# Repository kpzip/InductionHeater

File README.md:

# InductionHeater
Induction Heater

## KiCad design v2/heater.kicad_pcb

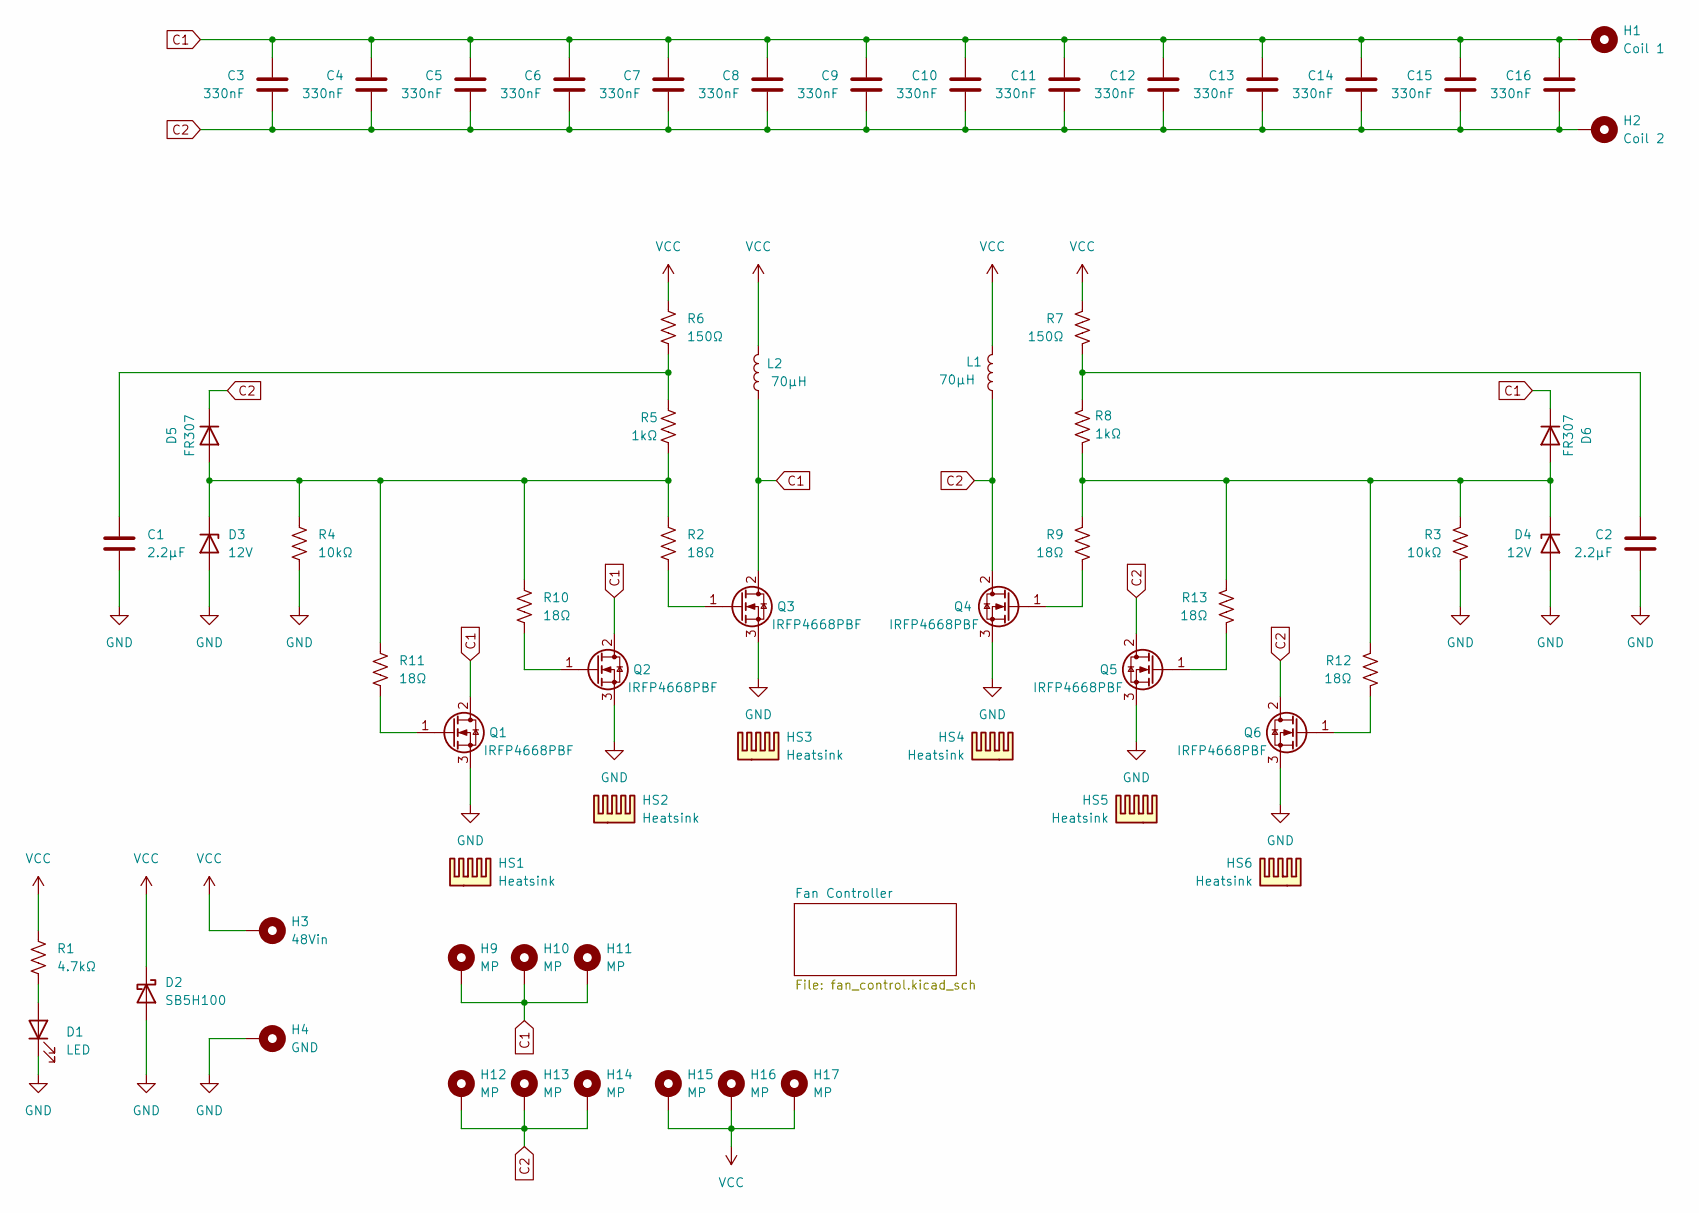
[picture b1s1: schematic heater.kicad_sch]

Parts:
C1, C2: 2.2μF; C_Disc_D4.3mm_W1.9mm_P5.00mm; Manufacturer Part Number FG26X7S2A225KRT06
C3, C4, C5, C6, C7, C8, C9, C10, C11, C12, C13, C14, C15, C16: 330nF; C_Rect_L31.5mm_W15.0mm_P27.50mm_MKS4; Manufacturer Part Number MKP1O133306F00KSSD
D1: LED; LED_D5.0mm; Manufacturer Part Number WP7113ID
D2: SB5H100; D_DO-201AD_P15.24mm_Horizontal; Manufacturer Part Number SB5H100-E3/54
D3, D4: 12V; D_DO-15_P15.24mm_Horizontal; Manufacturer Part Number 1N5349BRLG
D5, D6: FR307; D_DO-201AD_P15.24mm_Horizontal; Manufacturer Part Number FR307G
H1: Coil 1; MountingHole_8.4mm_M8_Pad
H2: Coil 2; MountingHole_8.4mm_M8_Pad
H3: 48Vin; MountingHole_8.4mm_M8_Pad
H4: GND; MountingHole_8.4mm_M8_Pad
H9, H10, H11, H12, H13, H14, H15, H16, H17: MP; MountingHole_3.2mm_M3_DIN965_Pad
HS1, HS2, HS3, HS4, HS5, HS6: Heatsink; 694-50; Manufacturer Part Number 694-50
L1, L2: 70μH; L_Toroid_Vertical_L39.9mm_W32.4mm_P30.0mm
Q1, Q2, Q3, Q4, Q5, Q6: IRFP4668PBF; TO-247-3_Vertical; Manufacturer Part Number IRFP4668PBFXKMA1
R1: 4.7kΩ; R_Axial_DIN0207_L6.3mm_D2.5mm_P10.16mm_Horizontal; Manufacturer Part Number CF12JT4K70
R2, R9, R10, R11, R12, R13: 18Ω; R_Axial_DIN0207_L6.3mm_D2.5mm_P10.16mm_Horizontal; Manufacturer Part Number CFR-50JB-52-18R
R3, R4: 10kΩ; R_Axial_DIN0207_L6.3mm_D2.5mm_P10.16mm_Horizontal; Manufacturer Part Number CF12JT10K0
R5, R8: 1kΩ; R_Axial_DIN0918_L18.0mm_D9.0mm_P30.48mm_Horizontal
R6, R7: 150Ω; R_Axial_DIN0918_L18.0mm_D9.0mm_P30.48mm_Horizontal

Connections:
C1: C3.1, C4.1, C5.1, C6.1, C7.1, C8.1, C9.1, C10.1, C11.1, C12.1, C13.1, C14.1, C15.1, C16.1, D6.1 (K), H1.1 (1_1), H9.1 (1_1), H10.1 (1_1), H11.1 (1_1), L2.1, Q1.2 (D), Q2.2 (D), Q3.2 (D)
C2: C3.2, C4.2, C5.2, C6.2, C7.2, C8.2, C9.2, C10.2, C11.2, C12.2, C13.2, C14.2, C15.2, C16.2, D5.1 (K), H2.1 (1_1), H12.1 (1_1), H13.1 (1_1), H14.1 (1_1), L1.1, Q4.2 (D), Q5.2 (D), Q6.2 (D)
GND: C1.2, C2.2, D1.1 (K), D2.2 (A), D3.2 (A), D4.2 (A), H4.1 (1_1), Q1.3 (S), Q2.3 (S), Q3.3 (S), Q4.3 (S), Q5.3 (S), Q6.3 (S), R3.2, R4.2; also elsewhere on the board
unnamed: C1.1, R5.1, R6.2
unnamed: C2.1, R7.2, R8.1
unnamed: D1.2 (A), R1.2
unnamed: D3.1 (K), D5.2 (A), R2.1, R4.1, R5.2, R10.1, R11.1
unnamed: D4.1 (K), D6.2 (A), R3.1, R8.2, R9.1, R12.1, R13.1
unnamed: Q1.1 (G), R11.2
unnamed: Q2.1 (G), R10.2
unnamed: Q3.1 (G), R2.2
unnamed: Q4.1 (G), R9.2
unnamed: Q5.1 (G), R13.2
unnamed: Q6.1 (G), R12.2
VCC: D2.1 (K), H3.1 (1_1), H15.1 (1_1), H16.1 (1_1), H17.1 (1_1), L1.2, L2.2, R1.1, R6.1, R7.1; also elsewhere on the board

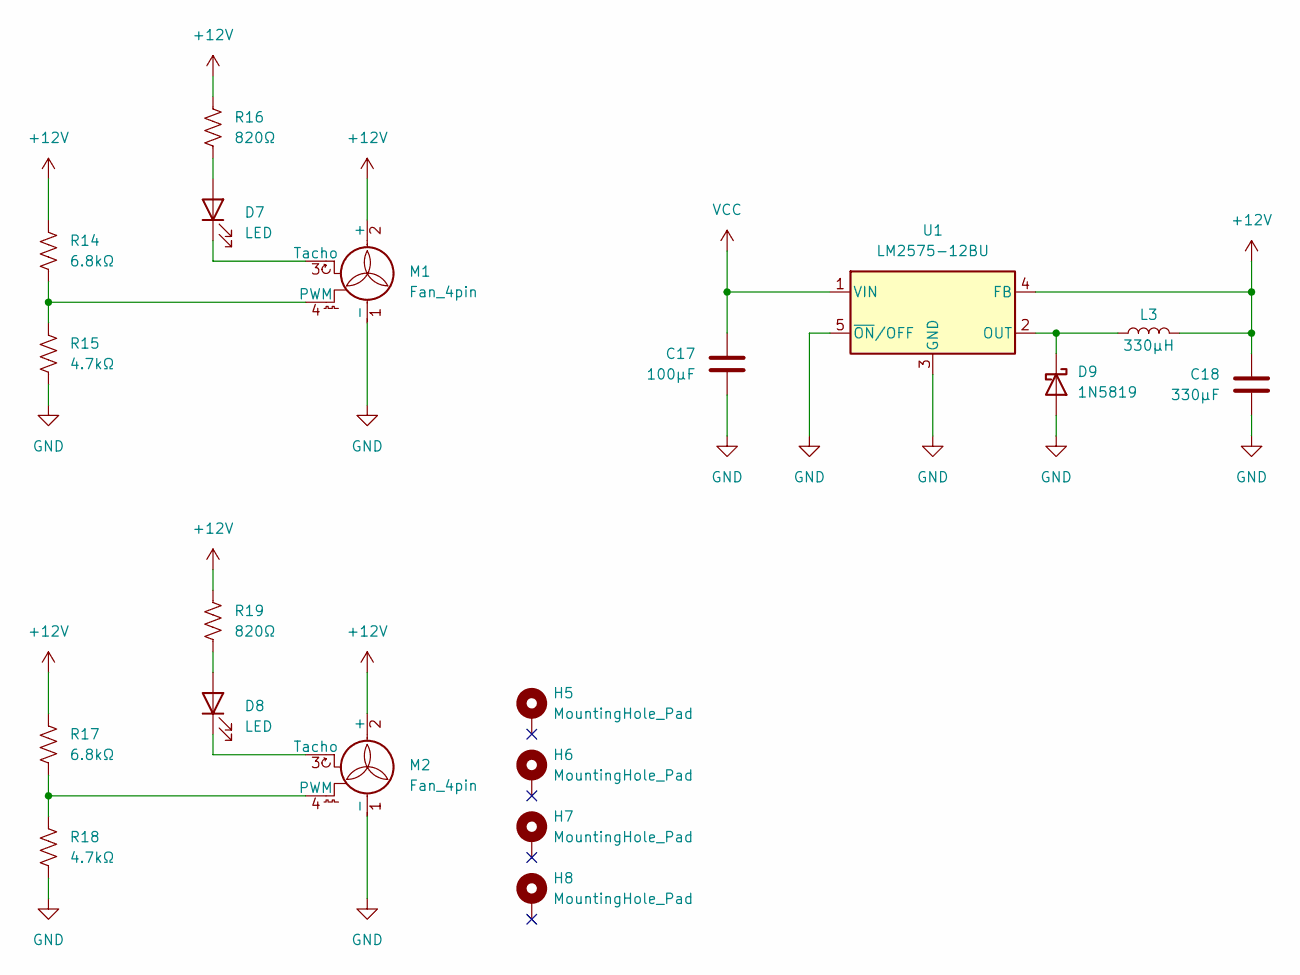
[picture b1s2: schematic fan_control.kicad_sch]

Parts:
C17: 100μF; C_Radial_D10.0mm_H20.0mm_P5.00mm; Manufacturer Part Number 100ZLH100MEFC10X20
C18: 330μF; C_Radial_D12.5mm_H25.0mm_P5.00mm; Manufacturer Part Number UVZ2A331MHD1TO
D7, D8: LED; LED_D5.0mm; Manufacturer Part Number WP7113ID
D9: 1N5819; D_DO-41_SOD81_P10.16mm_Horizontal; Manufacturer Part Number 1N5819
H5, H6, H7, H8: MountingHole_Pad; MountingHole_5.3mm_M5_DIN965_Pad
L3: 330μH; WE-PD_1210; Manufacturer Part Number 7447709331
M1, M2: Fan_4pin; Molex_KK-254_AE-6410-04A_1x04_P2.54mm_Vertical; Manufacturer Part Number 0022292041
R14, R17: 6.8kΩ; R_1206_3216Metric_Pad1.30x1.75mm_HandSolder; Manufacturer Part Number RC1206FR-076K8L
R15, R18: 4.7kΩ; R_1206_3216Metric_Pad1.30x1.75mm_HandSolder; Manufacturer Part Number RC1206FR-074K7L
R16, R19: 820Ω; R_1206_3216Metric_Pad1.30x1.75mm_HandSolder; Manufacturer Part Number CRGCQ1206F820R
U1: LM2575-12BU; TO-263-5_TabPin3; Manufacturer Part Number LM2575HVS-12/NOPB

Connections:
+12V: C18.1, L3.2, M1.2 (+), M2.2 (+), R14.1, R16.1, R17.1, R19.1, U1.4 (FB)
GND: C17.2, C18.2, D9.2 (A), M1.1 (-), M2.1 (-), R15.2, R18.2, U1.3 (GND), U1.5 (~ON/OFF); also elsewhere on the board
unnamed: D7.2 (A), R16.2
unnamed: D7.1 (K), M1.3 (Tacho)
unnamed: D8.2 (A), R19.2
unnamed: D8.1 (K), M2.3 (Tacho)
unnamed: D9.1 (K), L3.1, U1.2 (OUT)
unnamed: M1.4 (PWM), R14.2, R15.1
unnamed: M2.4 (PWM), R17.2, R18.1
VCC: C17.1, U1.1 (VIN); also elsewhere on the board

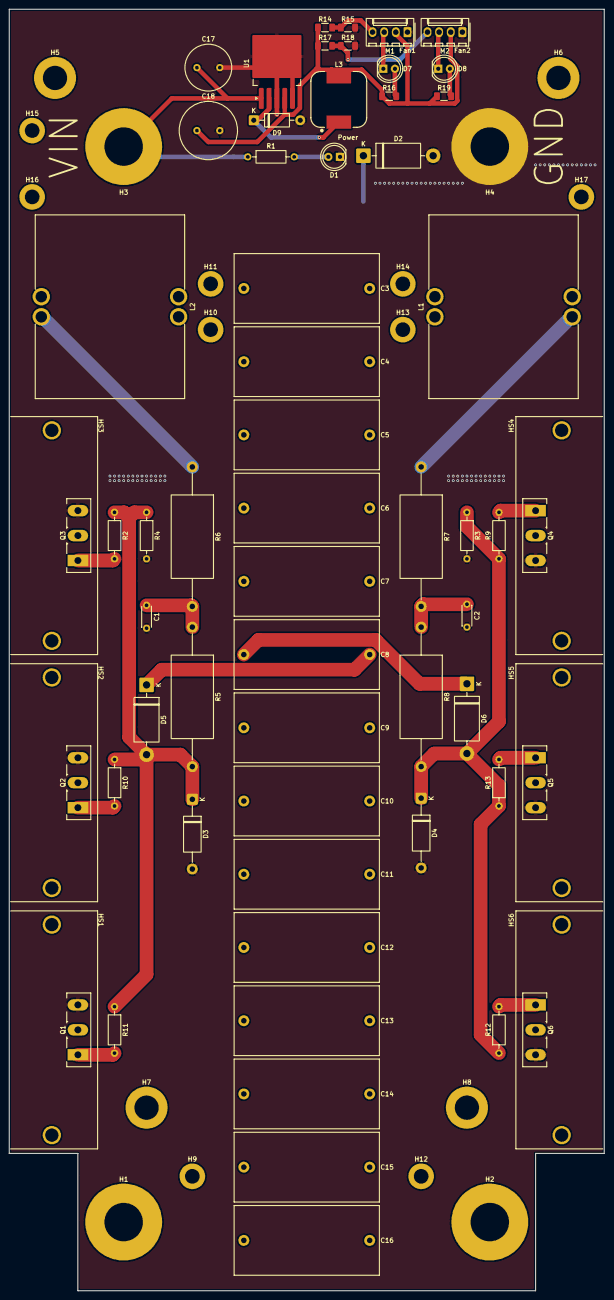
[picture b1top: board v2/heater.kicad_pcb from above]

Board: 2 copper layers, 130.0 x 280.0 mm, 81 parts (0 on the bottom side), 23 nets.

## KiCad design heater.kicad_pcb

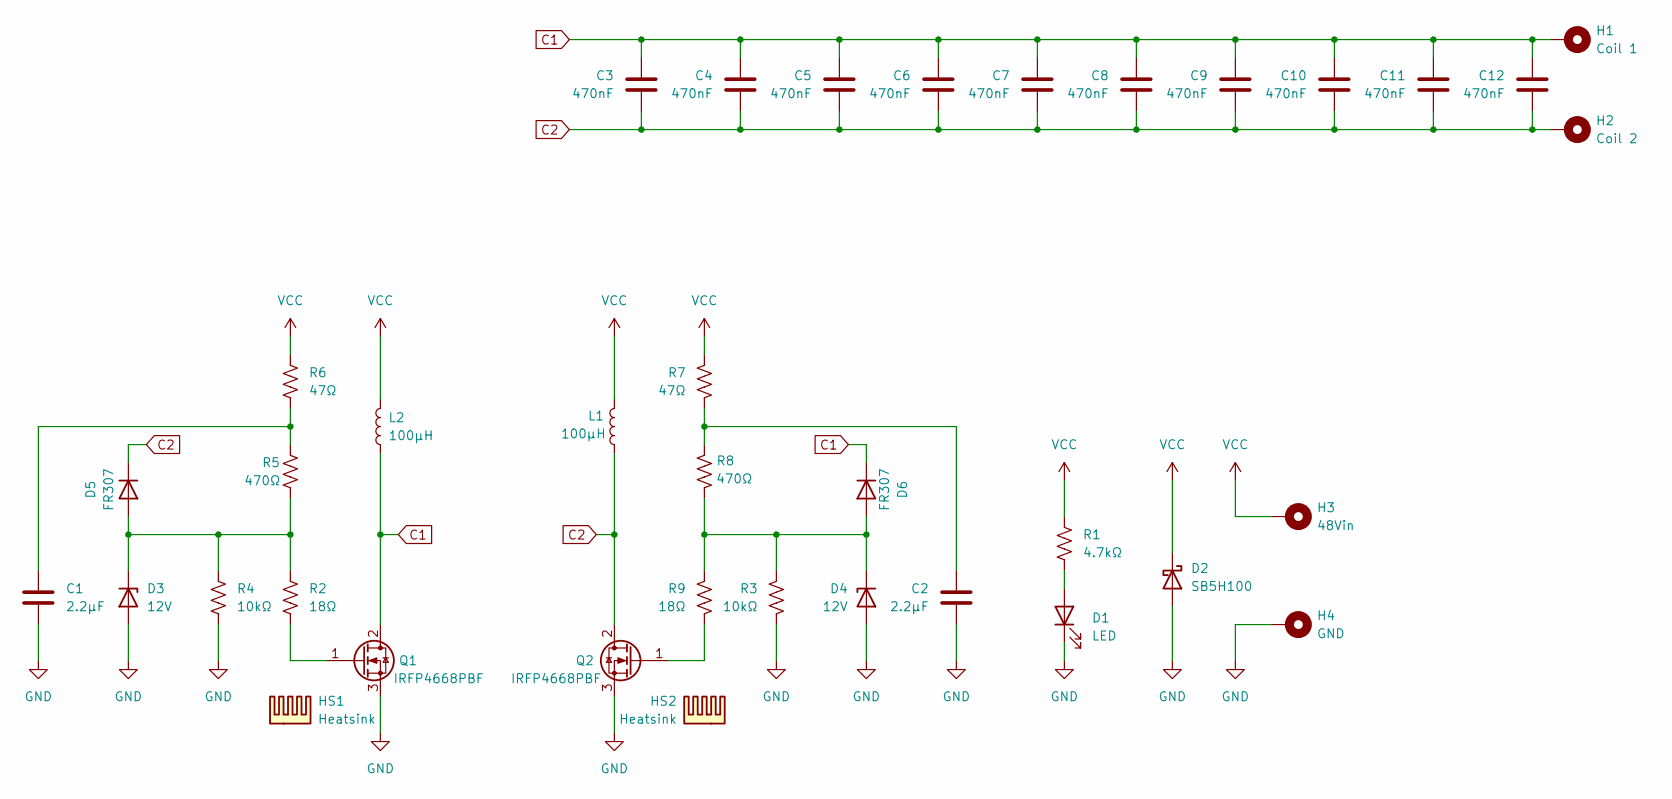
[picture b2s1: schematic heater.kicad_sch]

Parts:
C1, C2: 2.2μF; C_Disc_D4.3mm_W1.9mm_P5.00mm; Manufacturer Part Number FG26X7S2A225KRT06
C3, C4, C5, C6, C7, C8, C9, C10, C11, C12: 470nF; C_Rect_L31.5mm_W11.0mm_P27.50mm_MKS4; Manufacturer Part Number MKP1J034706B00KSSD
D1: LED; LED_D5.0mm; Manufacturer Part Number WP7113ID
D2: SB5H100; D_DO-201AD_P15.24mm_Horizontal; Manufacturer Part Number SB5H100-E3/54
D3, D4: 12V; D_DO-15_P15.24mm_Horizontal; Manufacturer Part Number 1N5349BRLG
D5, D6: FR307; D_DO-201AD_P15.24mm_Horizontal; Manufacturer Part Number FR307G
H1: Coil 1; MountingHole_8.4mm_M8_Pad
H2: Coil 2; MountingHole_8.4mm_M8_Pad
H3: 48Vin; MountingHole_8.4mm_M8_Pad
H4: GND; MountingHole_8.4mm_M8_Pad
HS1, HS2: Heatsink; Manufacturer Part Number 694-50
L1, L2: 100μH; L_Toroid_Vertical_L31.8mm_W15.9mm_P13.50mm_Bourns_5700; Manufacturer Part Number 2312-V-RC
Q1, Q2: IRFP4668PBF; TO-247-3_Vertical; Manufacturer Part Number IRFP4668PBF
R1: 4.7kΩ; R_Axial_DIN0207_L6.3mm_D2.5mm_P10.16mm_Horizontal; Manufacturer Part Number CF12JT4K70
R2, R9: 18Ω; R_Axial_DIN0207_L6.3mm_D2.5mm_P10.16mm_Horizontal; Manufacturer Part Number CFR-50JB-52-18R
R3, R4: 10kΩ; R_Axial_DIN0207_L6.3mm_D2.5mm_P10.16mm_Horizontal; Manufacturer Part Number CF12JT10K0
R5, R8: 470Ω; R_Axial_DIN0918_L18.0mm_D9.0mm_P30.48mm_Horizontal; Manufacturer Part Number ROX5SSJ470R
R6, R7: 47Ω; R_Axial_DIN0918_L18.0mm_D9.0mm_P30.48mm_Horizontal; Manufacturer Part Number ROX5SSJ47R

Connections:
C1: C3.1, C4.1, C5.1, C6.1, C7.1, C8.1, C9.1, C10.1, C11.1, C12.1, D6.1 (K), H1.1, L2.1, Q1.2 (D)
C2: C3.2, C4.2, C5.2, C6.2, C7.2, C8.2, C9.2, C10.2, C11.2, C12.2, D5.1 (K), H2.1, L1.1, Q2.2 (D)
GND: C1.2, C2.2, D1.1 (K), D2.2 (A), D3.2 (A), D4.2 (A), H4.1, Q1.3 (S), Q2.3 (S), R3.2, R4.2
unnamed: C1.1, R5.1, R6.2
unnamed: C2.1, R7.2, R8.1
unnamed: D1.2 (A), R1.2
unnamed: D3.1 (K), D5.2 (A), R2.1, R4.1, R5.2
unnamed: D4.1 (K), D6.2 (A), R3.1, R8.2, R9.1
unnamed: Q1.1 (G), R2.2
unnamed: Q2.1 (G), R9.2
VCC: D2.1 (K), H3.1, L1.2, L2.2, R1.1, R6.1, R7.1

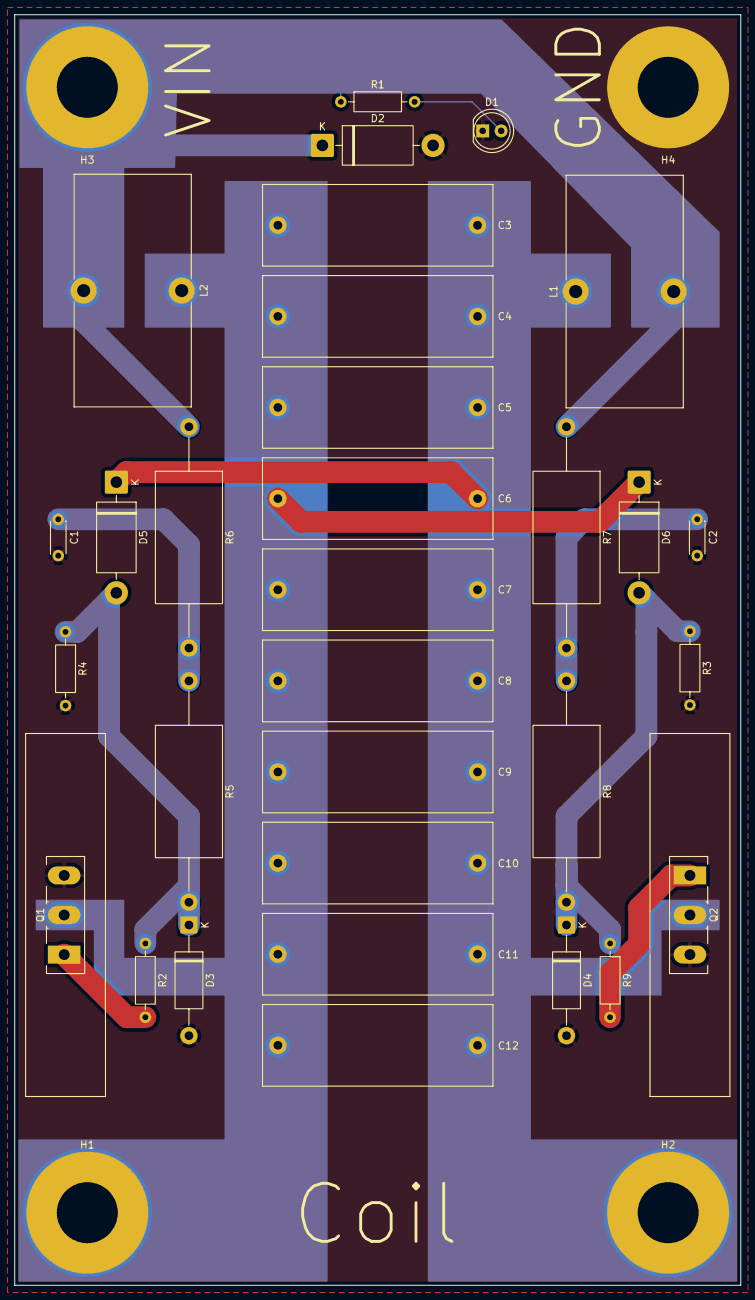
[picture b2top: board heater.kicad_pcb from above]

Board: 2 copper layers, 100.0 x 175.0 mm, 35 parts (0 on the bottom side), 11 nets.

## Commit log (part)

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2025-12-19 plot
2026-01-21 fix mosfet part No.
2026-04-05 move v1
2026-04-05 v2 (DEATH)
2026-04-05 work on v2
2026-04-06 fixes
2026-04-06 final touches
2026-04-08 model plates
